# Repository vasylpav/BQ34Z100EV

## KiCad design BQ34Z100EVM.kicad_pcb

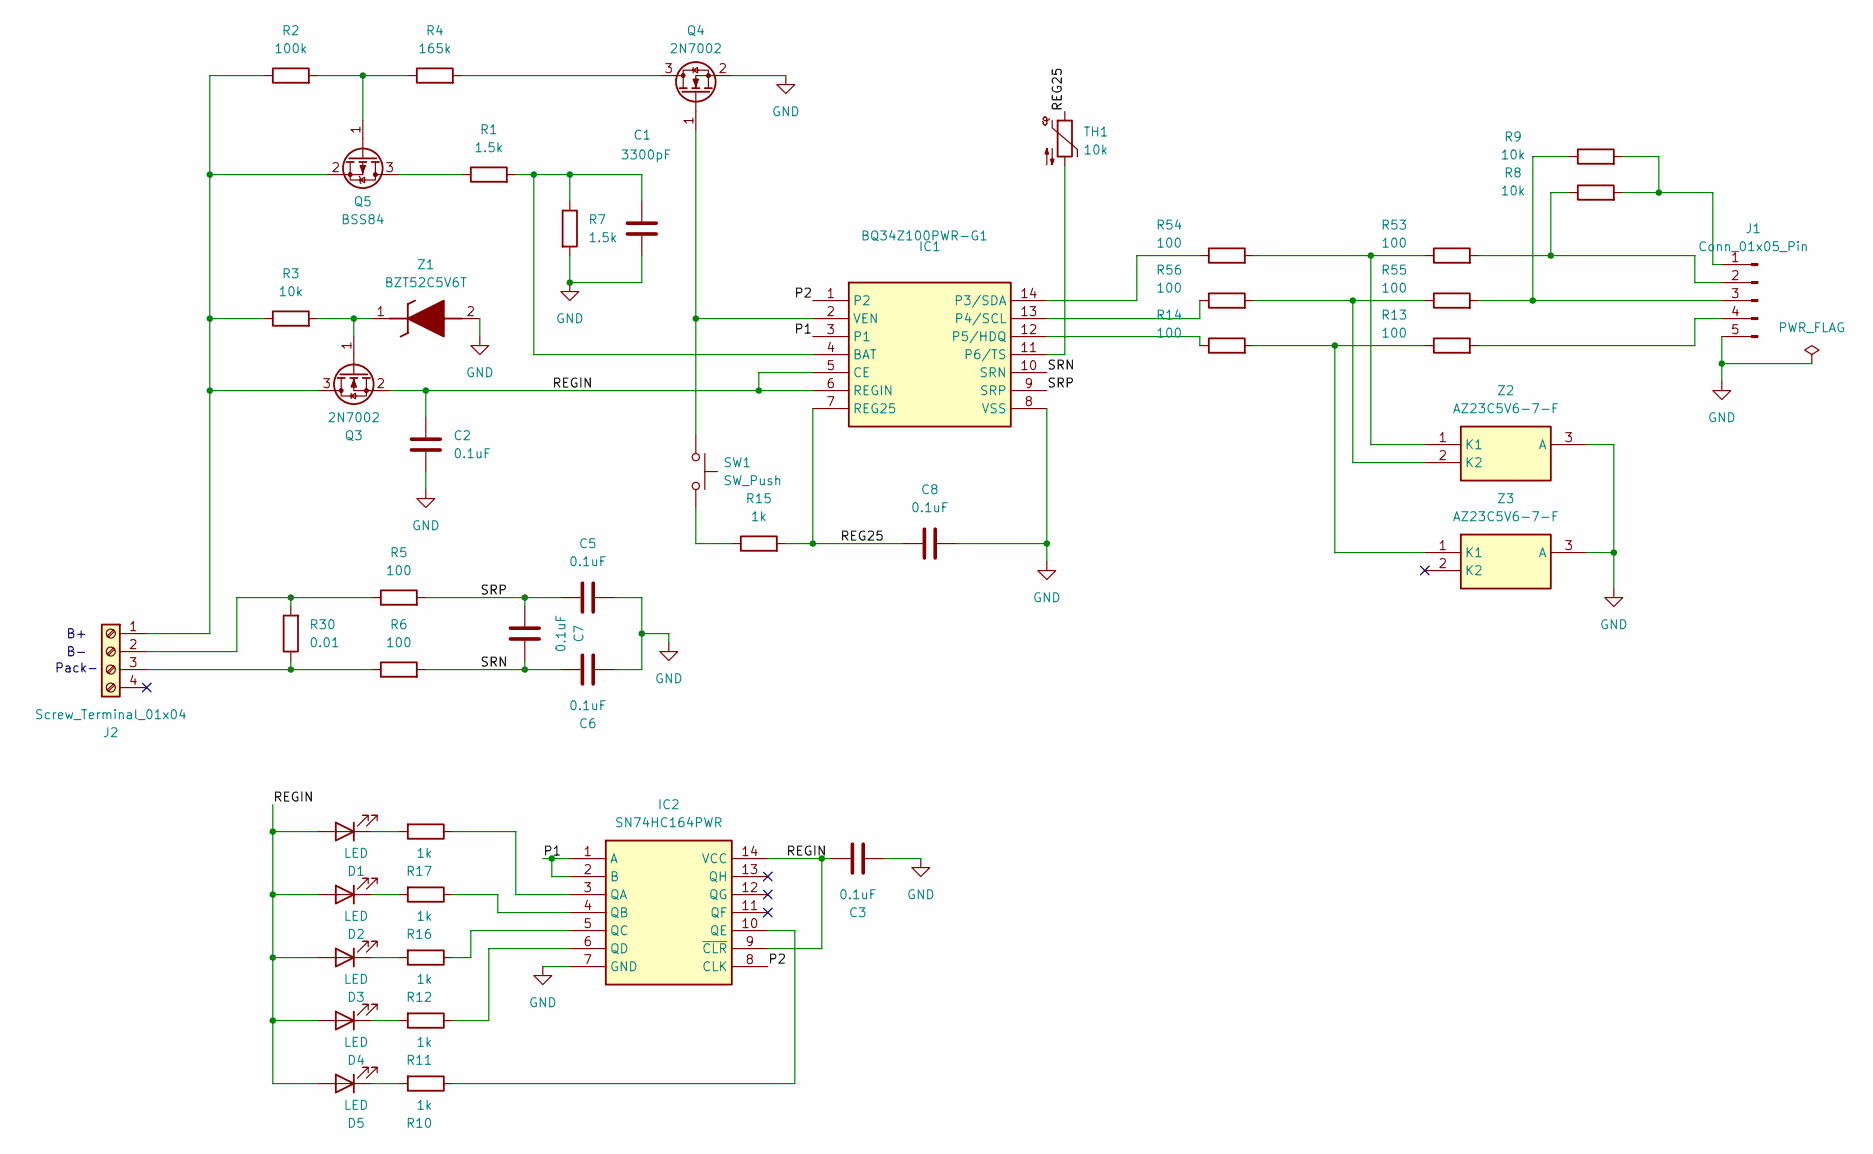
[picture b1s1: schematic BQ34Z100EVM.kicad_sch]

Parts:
C1: 3300pF; C_1206_3216Metric_Pad1.33x1.80mm_HandSolder
C2, C3, C5, C6, C7, C8: 0.1uF; C_1206_3216Metric_Pad1.33x1.80mm_HandSolder
D1, D2, D3, D4, D5: LED; LED_1206_3216Metric_Pad1.42x1.75mm_HandSolder
IC1: BQ34Z100PWR-G1; SOP65P640X120-14N; Manufacturer_Part_Number BQ34Z100PWR-G1; Mouser Part Number 595-BQ34Z100PWR-G1
IC2: SN74HC164PWR; SOP65P640X120-14N; Manufacturer_Part_Number SN74HC164PWR; Mouser Part Number 595-SN74HC164PWR
J1: Conn_01x05_Pin; PinHeader_1x05_P2.54mm_Vertical
J2: Screw_Terminal_01x04; TerminalBlock_Phoenix_MKDS-1,5-4-5.08_1x04_P5.08mm_Horizont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
Q3, Q4: 2N7002; SOT-23
Q5: BSS84; SOT-23
R1, R7: 1.5k; R_1206_3216Metric_Pad1.30x1.75mm_HandSolder
R2: 100k; R_1206_3216Metric_Pad1.30x1.75mm_HandSolder
R3, R8, R9: 10k; R_1206_3216Metric_Pad1.30x1.75mm_HandSolder
R4: 165k; R_1206_3216Metric_Pad1.30x1.75mm_HandSolder
R5, R6, R13, R14, R53, R54, R55, R56: 100; R_1206_3216Metric_Pad1.30x1.75mm_HandSolder
R10, R11, R12, R15, R16, R17: 1k; R_1206_3216Metric_Pad1.30x1.75mm_HandSolder
R30: 0.01; R_2512_6332Metric_Pad1.40x3.35mm_HandSolder
SW1: SW_Push; SW_Push_1P1T_NO_CK_KSC6xxG
TH1: 10k; R_Axial_DIN0204_L3.6mm_D1.6mm_P5.08mm_Horizontal
Z1: BZT52C5V6T; SODFL1608X70N; Manufacturer_Part_Number BZT52C5V6T
Z2, Z3: AZ23C5V6-7-F; SOT96P240X115-3N; Manufacturer_Part_Number AZ23C5V6-7-F; Mouser Part Number 621-AZ23C5V6-F

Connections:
/P1: IC1.3 (P1), IC2.1 (A), IC2.2 (B)
/P2: IC1.1 (P2), IC2.8 (CLK)
/REG25: C8.1, IC1.7 (REG25), R15.2, TH1.1
/REGIN: C2.1, C3.2, D1.2 (A), D2.2 (A), D3.2 (A), D4.2 (A), D5.2 (A), IC1.5 (CE), IC1.6 (REGIN), IC2.9 (~CLR), IC2.14 (VCC), Q3.2 (S)
/SRN: C6.2, C7.2, IC1.10 (SRN), R6.2
/SRP: C5.1, C7.1, IC1.9 (SRP), R5.2
GND: C1.2, C2.2, C3.1, C5.2, C6.1, C8.2, IC1.8 (VSS), IC2.7 (GND), J1.5, Q4.2 (S), R7.2, Z1.2 (A), Z2.3 (A), Z3.3 (A)
unnamed: D1.1 (K), R17.2
unnamed: D2.1 (K), R16.2
unnamed: D3.1 (K), R12.2
unnamed: D4.1 (K), R11.2
unnamed: D5.1 (K), R10.2
unnamed: C1.1, IC1.4 (BAT), R1.2, R7.1
unnamed: IC1.14 (P3/SDA), R54.1
unnamed: IC1.13 (P4/SCL), R56.1
unnamed: IC1.12 (P5/HDQ), R14.1
unnamed: IC1.11 (P6/TS), TH1.2
unnamed: IC1.2 (VEN), Q4.1 (G), SW1.1
unnamed: IC2.3 (QA), R17.1
unnamed: IC2.4 (QB), R16.1
unnamed: IC2.5 (QC), R12.1
unnamed: IC2.6 (QD), R11.1
unnamed: IC2.10 (QE), R10.1
unnamed: J1.1, R8.2, R9.2
unnamed: J1.2, R8.1, R53.2
unnamed: J1.3, R9.1, R55.2
unnamed: J1.4, R13.2
unnamed: J2.1, Q3.3 (D), Q5.2 (S), R2.1, R3.1
unnamed: J2.2, R5.1, R30.2
unnamed: J2.3, R6.1, R30.1
unnamed: Q3.1 (G), R3.2, Z1.1 (K)
unnamed: Q4.3 (D), R4.2
unnamed: Q5.3 (D), R1.1
unnamed: Q5.1 (G), R2.2, R4.1
unnamed: R15.1, SW1.2
unnamed: R53.1, R54.2, Z2.1 (K1)
unnamed: R55.1, R56.2, Z2.2 (K2)
unnamed: R13.1, R14.2, Z3.1 (K1)

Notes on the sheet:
Pack-

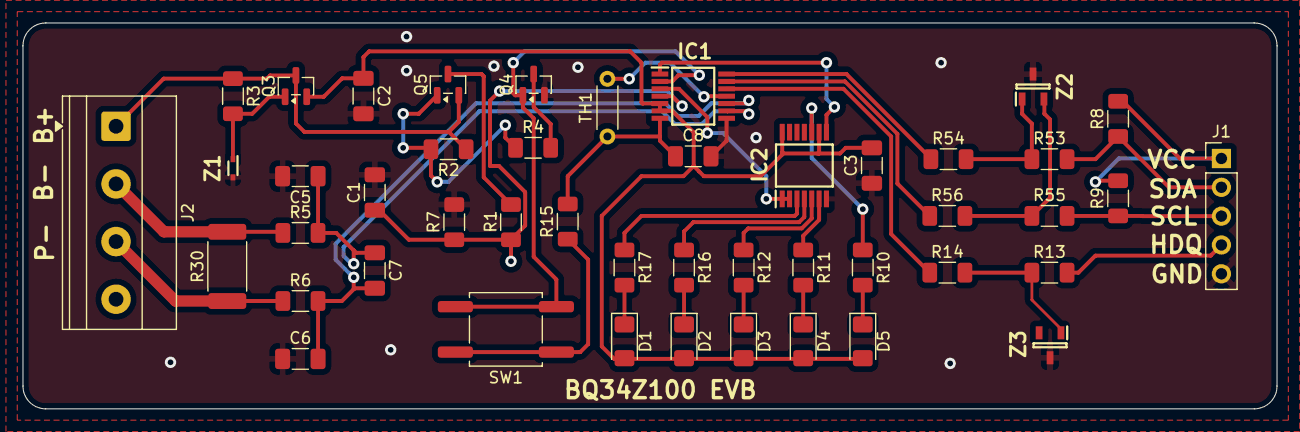
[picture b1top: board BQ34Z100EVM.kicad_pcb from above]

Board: 2 copper layers, 110.5 x 34.0 mm, 46 parts (0 on the bottom side), 38 nets.

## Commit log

2026-02-03 added schematic
2026-02-04 updated schematic
2026-02-09 added minor changes
2026-02-11 minor changes
